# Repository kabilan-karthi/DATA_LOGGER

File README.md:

View this project on [CADLAB.io](https://cadlab.io/project/29202). 

# DATA_LOGGER

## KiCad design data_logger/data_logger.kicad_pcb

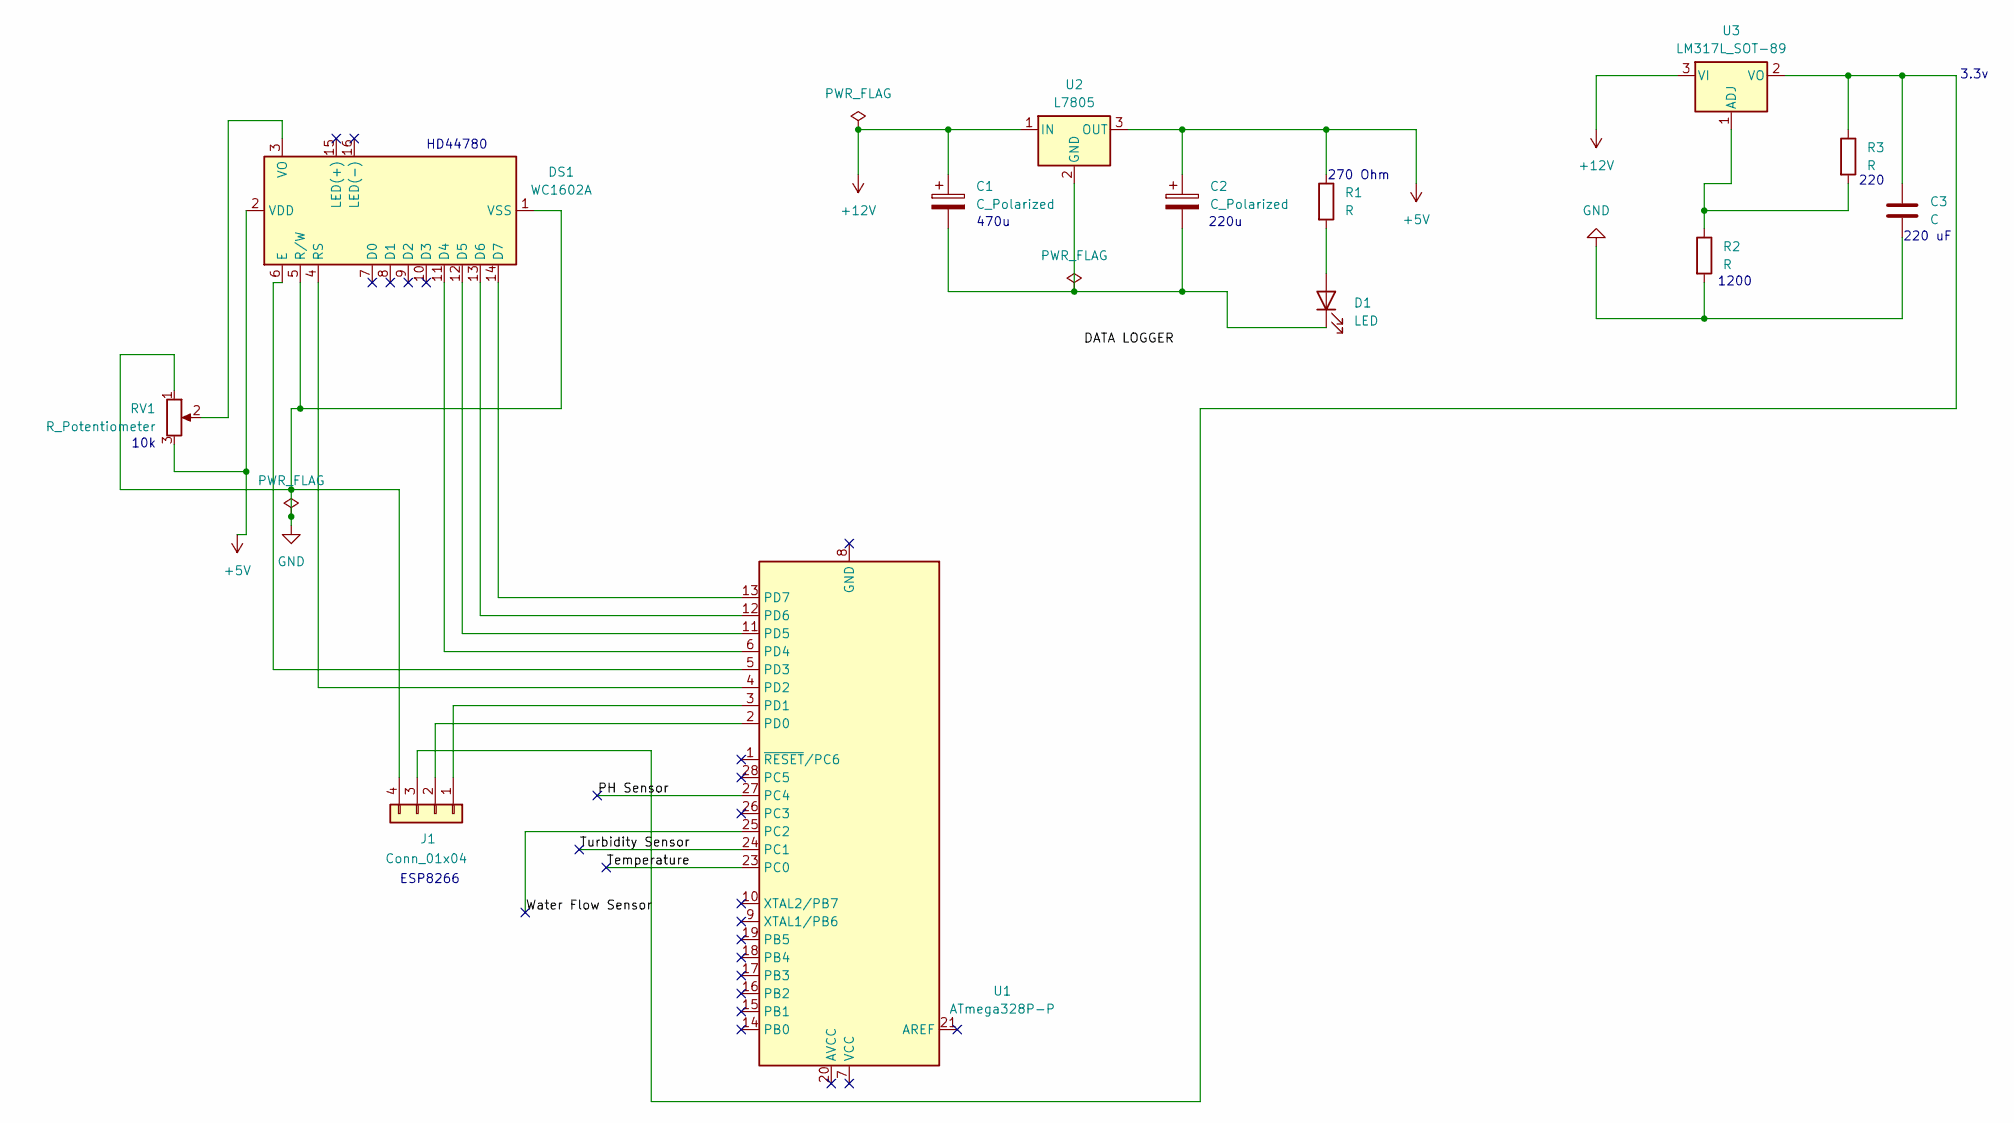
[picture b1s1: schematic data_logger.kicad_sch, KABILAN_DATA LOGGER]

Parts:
C1, C2: C_Polarized; CP_Radial_D5.0mm_P2.50mm
C3: C; C_Disc_D3.0mm_W1.6mm_P2.50mm
D1: LED; LED_D5.0mm
DS1: WC1602A
J1: Conn_01x04; LCD-016N002L
R1, R2, R3: R; R_Axial_DIN0207_L6.3mm_D2.5mm_P15.24mm_Horizontal
RV1: R_Potentiometer; Potentiometer_Piher_PT-10-V10_Vertical
U1: ATmega328P-P; DIP-28_W7.62mm
U2: L7805; TO-220F-4_P5.08x2.05mm_StaggerEven_Lead1.85mm_Vertical
U3: LM317L_SOT-89; SOT-89-3

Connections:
+5V: C2.1, DS1.2 (VDD), R1.1, RV1.3, U2.3 (OUT)
+12V: C1.1, U2.1 (IN), U3.3 (VI)
/PH Sensor: U1.27 (PC4)
/Temperature: U1.23 (PC0)
/Turbidity Sensor: U1.24 (PC1)
/Water Flow Sensor: U1.25 (PC2)
GND: C3.2, DS1.1 (VSS), DS1.5 (R/W), J1.4, R2.2, RV1.1
unnamed: D1.2 (A), R1.2
unnamed: C1.2, C2.2, D1.1 (K), U2.2 (GND)
unnamed: DS1.11 (D4), U1.6 (PD4)
unnamed: DS1.12 (D5), U1.11 (PD5)
unnamed: DS1.13 (D6), U1.12 (PD6)
unnamed: DS1.14 (D7), U1.13 (PD7)
unnamed: DS1.6 (E), U1.5 (PD3)
unnamed: DS1.4 (RS), U1.4 (PD2)
unnamed: DS1.3 (VO), RV1.2
unnamed: J1.1, U1.3 (PD1)
unnamed: J1.2, U1.2 (PD0)
unnamed: C3.1, J1.3, R3.1, U3.2 (VO)
unnamed: R2.1, R3.2, U3.1 (ADJ)

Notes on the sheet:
220u
220
220 uF
HD44780
ESP8266
10k
1200
270 Ohm
3.3v
470u

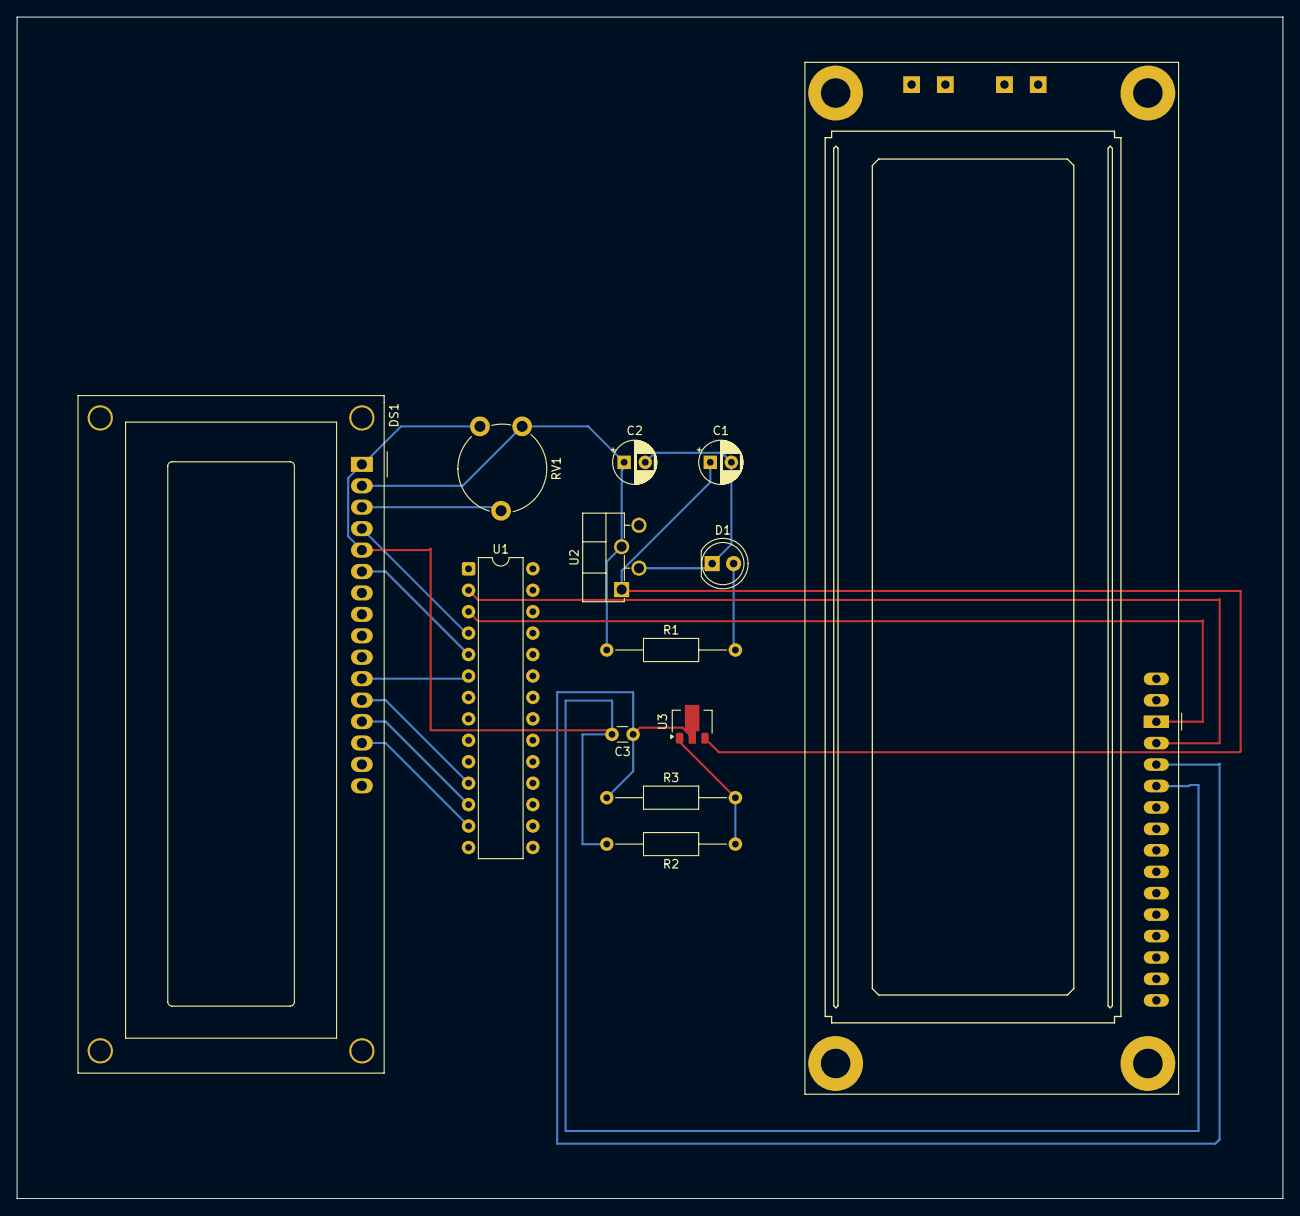
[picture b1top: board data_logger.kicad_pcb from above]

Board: 2 copper layers, 150.0 x 140.0 mm, 13 parts (0 on the bottom side), 16 nets.

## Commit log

2025-04-08 Backlink to CADLAB.io has been added.
